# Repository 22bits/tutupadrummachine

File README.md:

# tutupadrummachine
Tutupá machine is an arduino-based mechanical drum machine

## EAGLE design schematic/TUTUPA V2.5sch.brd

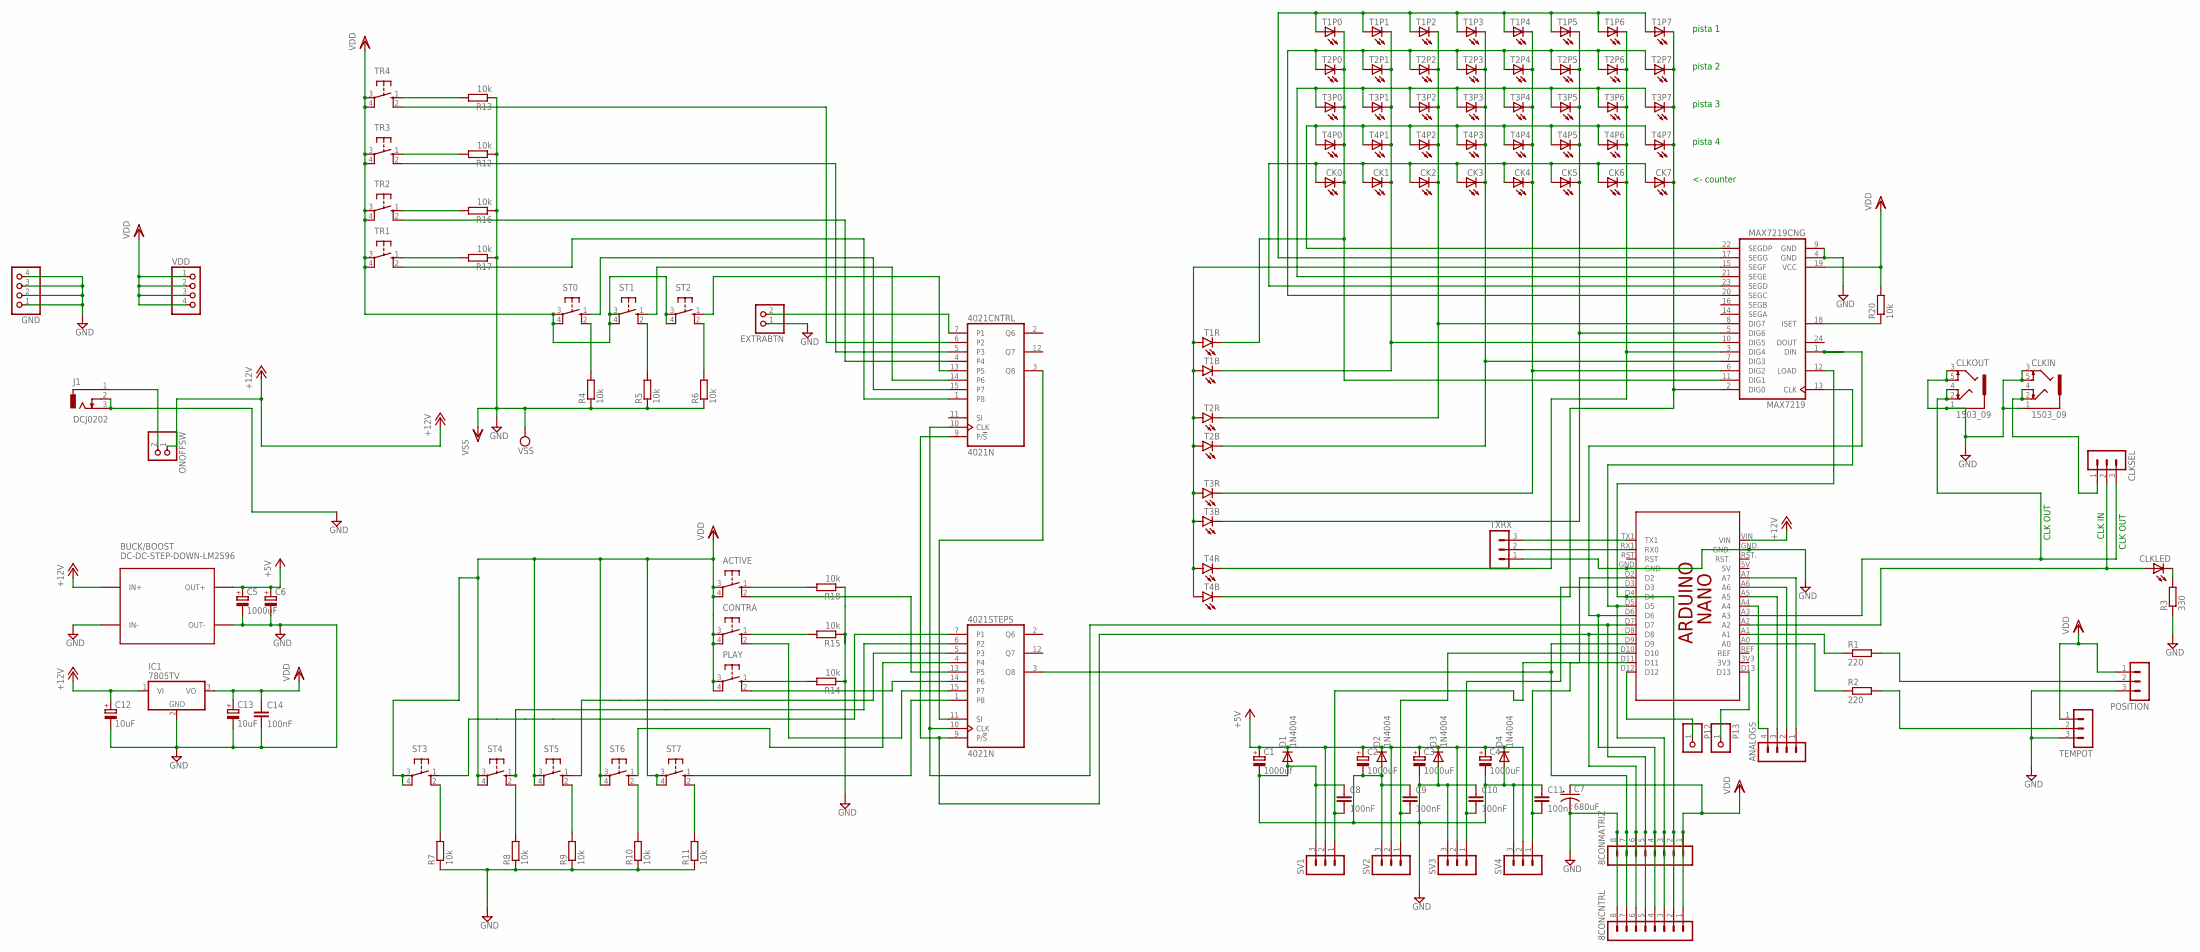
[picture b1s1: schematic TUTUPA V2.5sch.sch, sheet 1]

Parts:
8CONCNTRL, 8CONMATRIZ: MA08-1W
4021CNTRL, 4021STEPS: 4021N; DIL16
ACTIVE: 10-XX; B3F-10XX
ANALOGS: MA04-1
BUCK/BOOST: DC-DC-STEP-DOWN-LM2596
C1: 1000uf; E5-13
C2, C3, C4, C5: 1000uF; E5-13
C6: CPOL-EUE2.5-6; E2,5-6
C7: 680uF; E5-10,5
C8, C9, C10, C11, C14: 100nF; C050-024X044
C12, C13: 10uF; E1,8-4
CK0, CK1, CK2, CK3, CK4, CK5, CK6, CK7: LED5MM
CLKIN: 1503_09
CLKLED: LED5MM
CLKOUT: 1503_09
CLKSEL: MA03-1
CONTRA: 10-XX; B3F-10XX
D1, D2, D3, D4: 1N4004; DO41-10
EXTRABTN: PINHD-1X2; 1X02
GND: PINHD-1X4; 1X04
IC1: 7805TV; TO220V
J1: DCJ0202
MAX7219: MAX7219CNG; DIL24-3
ONOFFSW: PINHD-1X2; 1X02
P12, P13: PINHD-1X1; 1X01
PCB1: ARDUINO_NANO
PLAY: 10-XX; B3F-10XX
POSITION: MA03-1
R1, R2: 220; 0204/7
R3: 330; 0204/7
R4, R5, R6, R7, R8, R9, R10, R11, R12, R13, R14, R15, R16, R17, R18, R20: 10k; 0207/10
ST0, ST1, ST2, ST3, ST4, ST5, ST6, ST7: 10-XX; B3F-10XX
SV1, SV2, SV3, SV4: MA03-1
T1B, T1R, T2B, T2R, T3B, T3R, T4B, T4R: LED3MM
T1P0, T1P1, T1P2, T1P3, T1P4, T1P5, T1P6, T1P7, T2P0, T2P1, T2P2, T2P3, T2P4, T2P5, T2P6, T2P7, T3P0, T3P1, T3P2, T3P3, T3P4, T3P5, T3P6, T3P7, T4P0, T4P1, T4P2, T4P3, T4P4, T4P5, T4P6, T4P7: LED5MM
TEMPOT: MA03-1
TR1, TR2, TR3, TR4: 10-XX; B3F-10XX
TXRX: MA03-1
VDD: PINHD-1X4; 1X04

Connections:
+5V: BUCK/BOOST.OUT+, C1.+, C2.+, C3.+, C4.+, C5.+, C6.+, D1.C, D2.C, D3.C, D4.C, SV1.2, SV2.2, SV3.2, SV4.2
+12V: BUCK/BOOST.IN+, C12.+, IC1.1 (VI), ONOFFSW.1, PCB1.VIN
CLKINARDUINO: CLKLED.A, CLKSEL.2, PCB1.A2
CLKOUTARDUINO: CLKOUT.2, CLKOUT.4, CLKSEL.3, PCB1.A3
CONIN: CLKIN.2, CLKIN.4, CLKSEL.1
GND: 8CONCNTRL.8, 8CONMATRIZ.8, BUCK/BOOST.IN-, BUCK/BOOST.OUT-, C1.-, C2.-, C3.-, C4.-, C5.-, C6.-, C7.-, C8.1, C9.1, C10.1, C11.1, C12.-, C13.-, C14.2, CLKIN.1, CLKIN.3, CLKIN.5, CLKOUT.1, CLKOUT.3, CLKOUT.5, D1.A, D2.A, D3.A, D4.A, EXTRABTN.1, GND.1, GND.2, GND.3, GND.4, IC1.2 (GND), J1.2, J1.3, MAX7219.4 (GND), MAX7219.9 (GND), PCB1.GND, PCB1.GND., POSITION.3, R3.1, R4.1, R5.1, R6.1, R7.1, R8.1, R9.1, R10.1, R11.1, R12.1, R13.1, R14.1, R15.1, R16.1, R17.1, R18.1, SV1.3, SV2.3, SV3.3, SV4.3, TEMPOT.3, TXRX.1
unnamed: 4021CNTRL.14 (P6), ST1.1 (S)
unnamed: ANALOGS.3, PCB1.A5
unnamed: ANALOGS.2, PCB1.A6
unnamed: ANALOGS.1, PCB1.A7
unnamed: 4021CNTRL.13 (P5), ST2.1 (S)
unnamed: 4021CNTRL.7 (P1), EXTRABTN.2
unnamed: R8.2, ST4.2 (S1)
unnamed: 4021STEPS.1 (P8), ST7.1 (S)
unnamed: R17.2, TR1.1 (S)
unnamed: 4021CNTRL.15 (P7), ST0.1 (S)
unnamed: 4021CNTRL.1 (P8), TR1.2 (S1)
unnamed: 4021CNTRL.4, TR2.2 (S1)
unnamed: MAX7219.15 (SEGF), T1B.A, T1R.A, T2B.A, T2R.A, T3B.A, T3R.A, T4B.A, T4R.A
unnamed: 4021CNTRL.5 (P3), TR3.2 (S1)
unnamed: CONTRA.1 (S), R15.2
unnamed: 4021STEPS.14 (P6), PLAY.2 (S1)
unnamed: 4021STEPS.6 (P2), ST4.1 (S)
unnamed: 4021STEPS.5 (P3), ST5.1 (S)
unnamed: 4021CNTRL.6 (P2), TR4.2 (S1)
unnamed: PLAY.1 (S), R14.2
unnamed: R4.2, ST0.2 (S1)
unnamed: R5.2, ST1.2 (S1)
unnamed: R6.2, ST2.2 (S1)
unnamed: R7.2, ST3.2 (S1)
unnamed: 4021STEPS.7 (P1), ST3.1 (S)
unnamed: R9.2, ST5.2 (S1)
unnamed: R10.2, ST6.2 (S1)
unnamed: R11.2, ST7.2 (S1)
unnamed: R13.2, TR4.1 (S)
unnamed: R12.2, TR3.1 (S)
unnamed: R16.2, TR2.1 (S)
unnamed: 4021STEPS.4, ST6.1 (S)
unnamed: 4021STEPS.15 (P7), CONTRA.2 (S1)
unnamed: 4021STEPS.13 (P5), ACTIVE.2 (S1)
unnamed: ACTIVE.1 (S), R18.2
unnamed: 4021CNTRL.3 (Q8), 4021STEPS.11 (SI)
unnamed: 8CONCNTRL.5, 8CONMATRIZ.5, 4021CNTRL.10 (CLK), 4021STEPS.10 (CLK), PCB1.D7
unnamed: 8CONCNTRL.6, 8CONMATRIZ.6, 4021CNTRL.9 (P/!S), 4021STEPS.9 (P/!S), PCB1.D8
unnamed: 8CONCNTRL.3, 8CONMATRIZ.3, MAX7219.13 (CLK), PCB1.D5
unnamed: 8CONCNTRL.4, 8CONMATRIZ.4, MAX7219.1 (DIN), PCB1.D6
unnamed: 8CONCNTRL.7, 8CONMATRIZ.7, 4021STEPS.3 (Q8), PCB1.D9
unnamed: 8CONCNTRL.2, 8CONMATRIZ.2, MAX7219.12 (LOAD), PCB1.D4
unnamed: MAX7219.18 (ISET), R20.1
unnamed: CK0.A, CK1.A, CK2.A, CK3.A, CK4.A, CK5.A, CK6.A, CK7.A, MAX7219.23 (SEGD)
unnamed: R2.2, TEMPOT.2
unnamed: POSITION.2, R1.2
unnamed: ANALOGS.4, PCB1.A4
unnamed: J1.1, ONOFFSW.2
unnamed: PCB1.A1, R1.1
unnamed: PCB1.A0, R2.1
unnamed: MAX7219.21 (SEGE), T3P0.A, T3P1.A, T3P2.A, T3P3.A, T3P4.A, T3P5.A, T3P6.A, T3P7.A
unnamed: MAX7219.22 (SEGDP), T4P0.A, T4P1.A, T4P2.A, T4P3.A, T4P4.A, T4P5.A, T4P6.A, T4P7.A
unnamed: CK0.K (C), MAX7219.11 (DIG1), T1P0.K (C), T1R.K (C), T2P0.K (C), T3P0.K (C), T4P0.K (C)
unnamed: CK1.K (C), MAX7219.10 (DIG5), T1B.K (C), T1P1.K (C), T2P1.K (C), T3P1.K (C), T4P1.K (C)
unnamed: CK2.K (C), MAX7219.8 (DIG7), T1P2.K (C), T2P2.K (C), T2R.K (C), T3P2.K (C), T4P2.K (C)
unnamed: CK3.K (C), MAX7219.7 (DIG3), T1P3.K (C), T2B.K (C), T2P3.K (C), T3P3.K (C), T4P3.K (C)
unnamed: CK4.K (C), MAX7219.6 (DIG2), T1P4.K (C), T2P4.K (C), T3P4.K (C), T3R.K (C), T4P4.K (C)
unnamed: CK5.K (C), MAX7219.5 (DIG6), T1P5.K (C), T2P5.K (C), T3B.K (C), T3P5.K (C), T4P5.K (C)
unnamed: CK6.K (C), MAX7219.3 (DIG4), T1P6.K (C), T2P6.K (C), T3P6.K (C), T4P6.K (C), T4R.K (C)
unnamed: CK7.K (C), MAX7219.2 (DIG0), T1P7.K (C), T2P7.K (C), T3P7.K (C), T4B.K (C), T4P7.K (C)
unnamed: MAX7219.17 (SEGG), T1P0.A, T1P1.A, T1P2.A, T1P3.A, T1P4.A, T1P5.A, T1P6.A, T1P7.A
unnamed: MAX7219.20 (SEGC), T2P0.A, T2P1.A, T2P2.A, T2P3.A, T2P4.A, T2P5.A, T2P6.A, T2P7.A
unnamed: PCB1.TX1, TXRX.3
unnamed: PCB1.RX1 (RX0), TXRX.2
unnamed: CLKLED.K (C), R3.2
unnamed: P12.1, PCB1.D12
unnamed: P13.1, PCB1.D13
unnamed: C8.2, PCB1.D11, SV1.1
unnamed: C9.2, PCB1.D10, SV2.1
unnamed: C10.2, PCB1.D3, SV3.1
unnamed: C11.2, PCB1.D2, SV4.1
VDD: 8CONCNTRL.1, 8CONMATRIZ.1, 4021CNTRL.16 (VDD), 4021STEPS.16 (VDD), ACTIVE.3, ACTIVE.4 (P1), C7.+, C13.+, C14.1, CONTRA.3, CONTRA.4 (P1), IC1.3 (VO), MAX7219.19 (VCC), PLAY.3, PLAY.4 (P1), POSITION.1, R20.2, ST0.3, ST0.4 (P1), ST1.3, ST1.4 (P1), ST2.3, ST2.4 (P1), ST3.3, ST3.4 (P1), ST4.3, ST4.4 (P1), ST5.3, ST5.4 (P1), ST6.3, ST6.4 (P1), ST7.3, ST7.4 (P1), TEMPOT.1, TR1.3, TR1.4 (P1), TR2.3, TR2.4 (P1), TR3.3, TR3.4 (P1), TR4.3, TR4.4 (P1), VDD.1, VDD.2, VDD.3, VDD.4
VSS: 4021CNTRL.8 (VSS), 4021STEPS.8 (VSS)

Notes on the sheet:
<- counter
pista 1
pista 2
pista 3
pista 4
CLK IN
CLK OUT

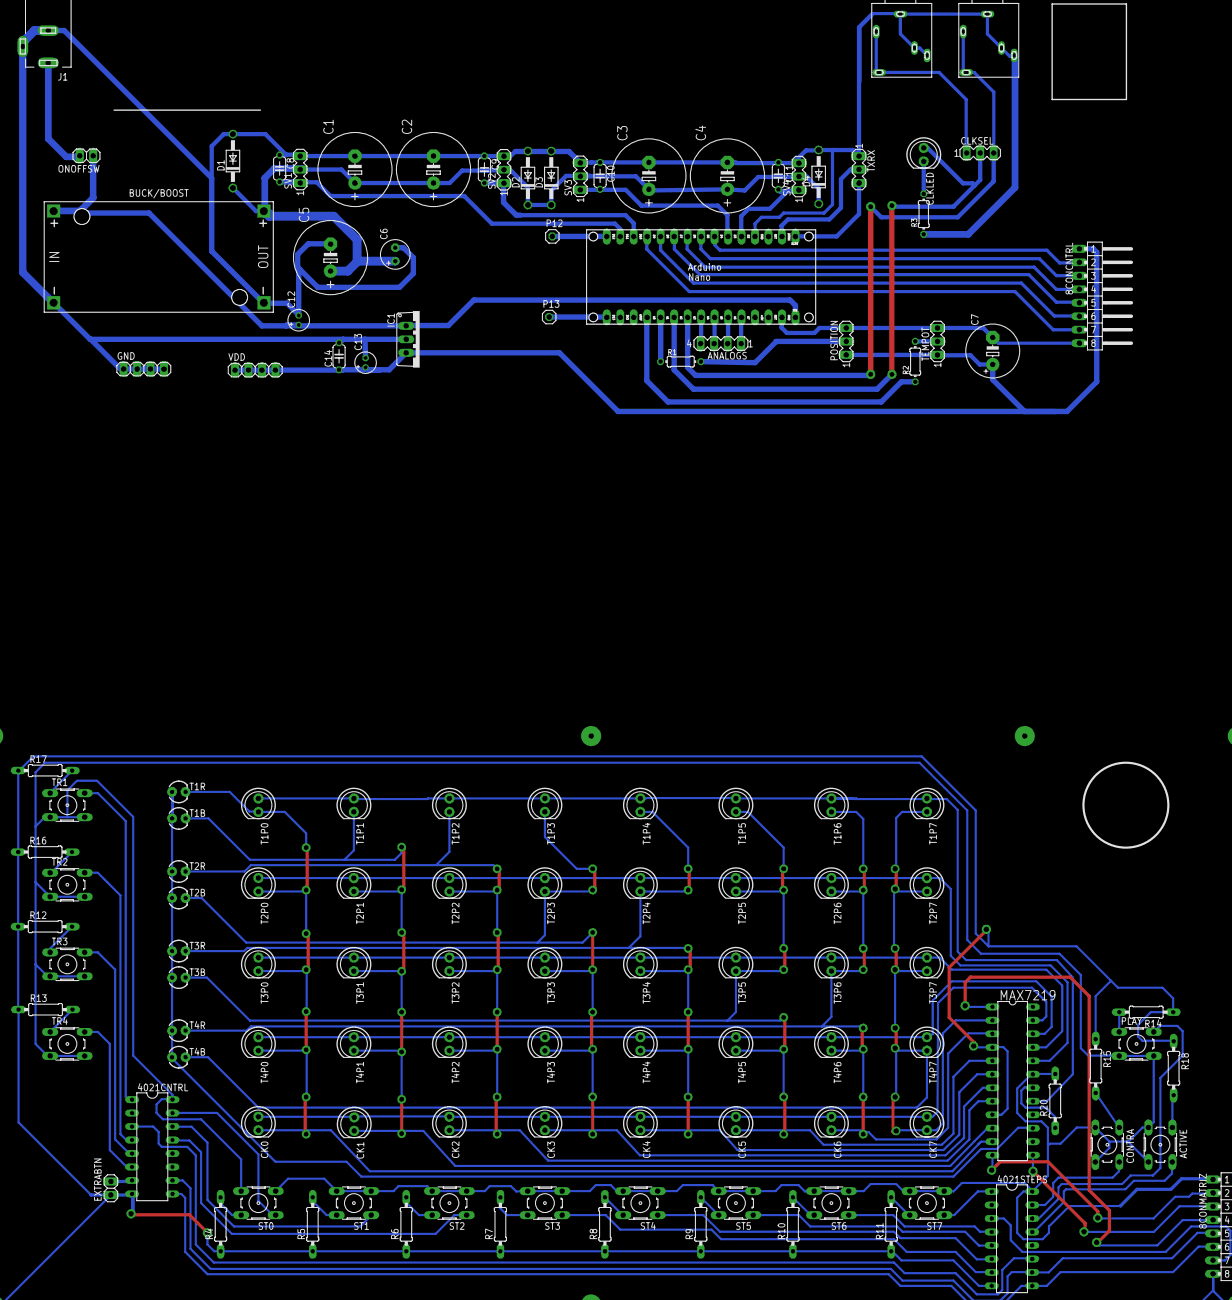
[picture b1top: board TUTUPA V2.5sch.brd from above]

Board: 2 copper layers, 127 parts (0 on the bottom side), 79 nets.

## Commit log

2017-04-18 Create code
2017-04-18 upload
    upload

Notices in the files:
parts and their libraries:
diy-modules: Released under the Creative Commons Attribution 4.0 International License: http://creativecommons.org/licenses/by/4.0
SparkFun-LED: Licensing: Creative Commons ShareAlike 4.0 International - https://creativecommons.org/licenses/by-sa/4.0
